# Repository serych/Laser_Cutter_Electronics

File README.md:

# Laser cutter electronics for Fluid NC

This is small laser cutter electronics board. The main goal of the development was to achieve a **board width of less than 4 cm** so that it could be easily mounted on standard 4020 profiles used in the construction of laser engravers. 
The board is designed for use with [Fluid NC software](http://wiki.fluidnc.com/en/home). 
## Electronics concept
The electronics are based on the **ESP32 WROOM** module, containing two **TMC2130 SPI** stepper motor drivers, a **PWM output for the laser**, and a **Micro SD card slot**. 
The initial programming of the ESP32 processor must be done via an **external USB-UART converter**; the board has a connector for this purpose. 
**!!!Make sure that the converter supplies the board with 3.3V (and not 5V)!!!** 
Further upgrades can be done using OTA. 

The board also includes an **Attiny 412 processor**, which controls a WS2812 **color status LED** (internal with the option of connecting one additional external LED). This processor can be programmed via the UPDI interface (there is a connector on the board for this purpose), which is again connected to the USB-UART converter. 
*The Attiny 412 processor with status LED is an **optional accessory**; the board works even without it.* 
## Files
The schematic and PCB layout were created in [KiCad](https://kicad.org) 9. The Gerber and drilling files for PCB production are stored in the "Gerber" directory.

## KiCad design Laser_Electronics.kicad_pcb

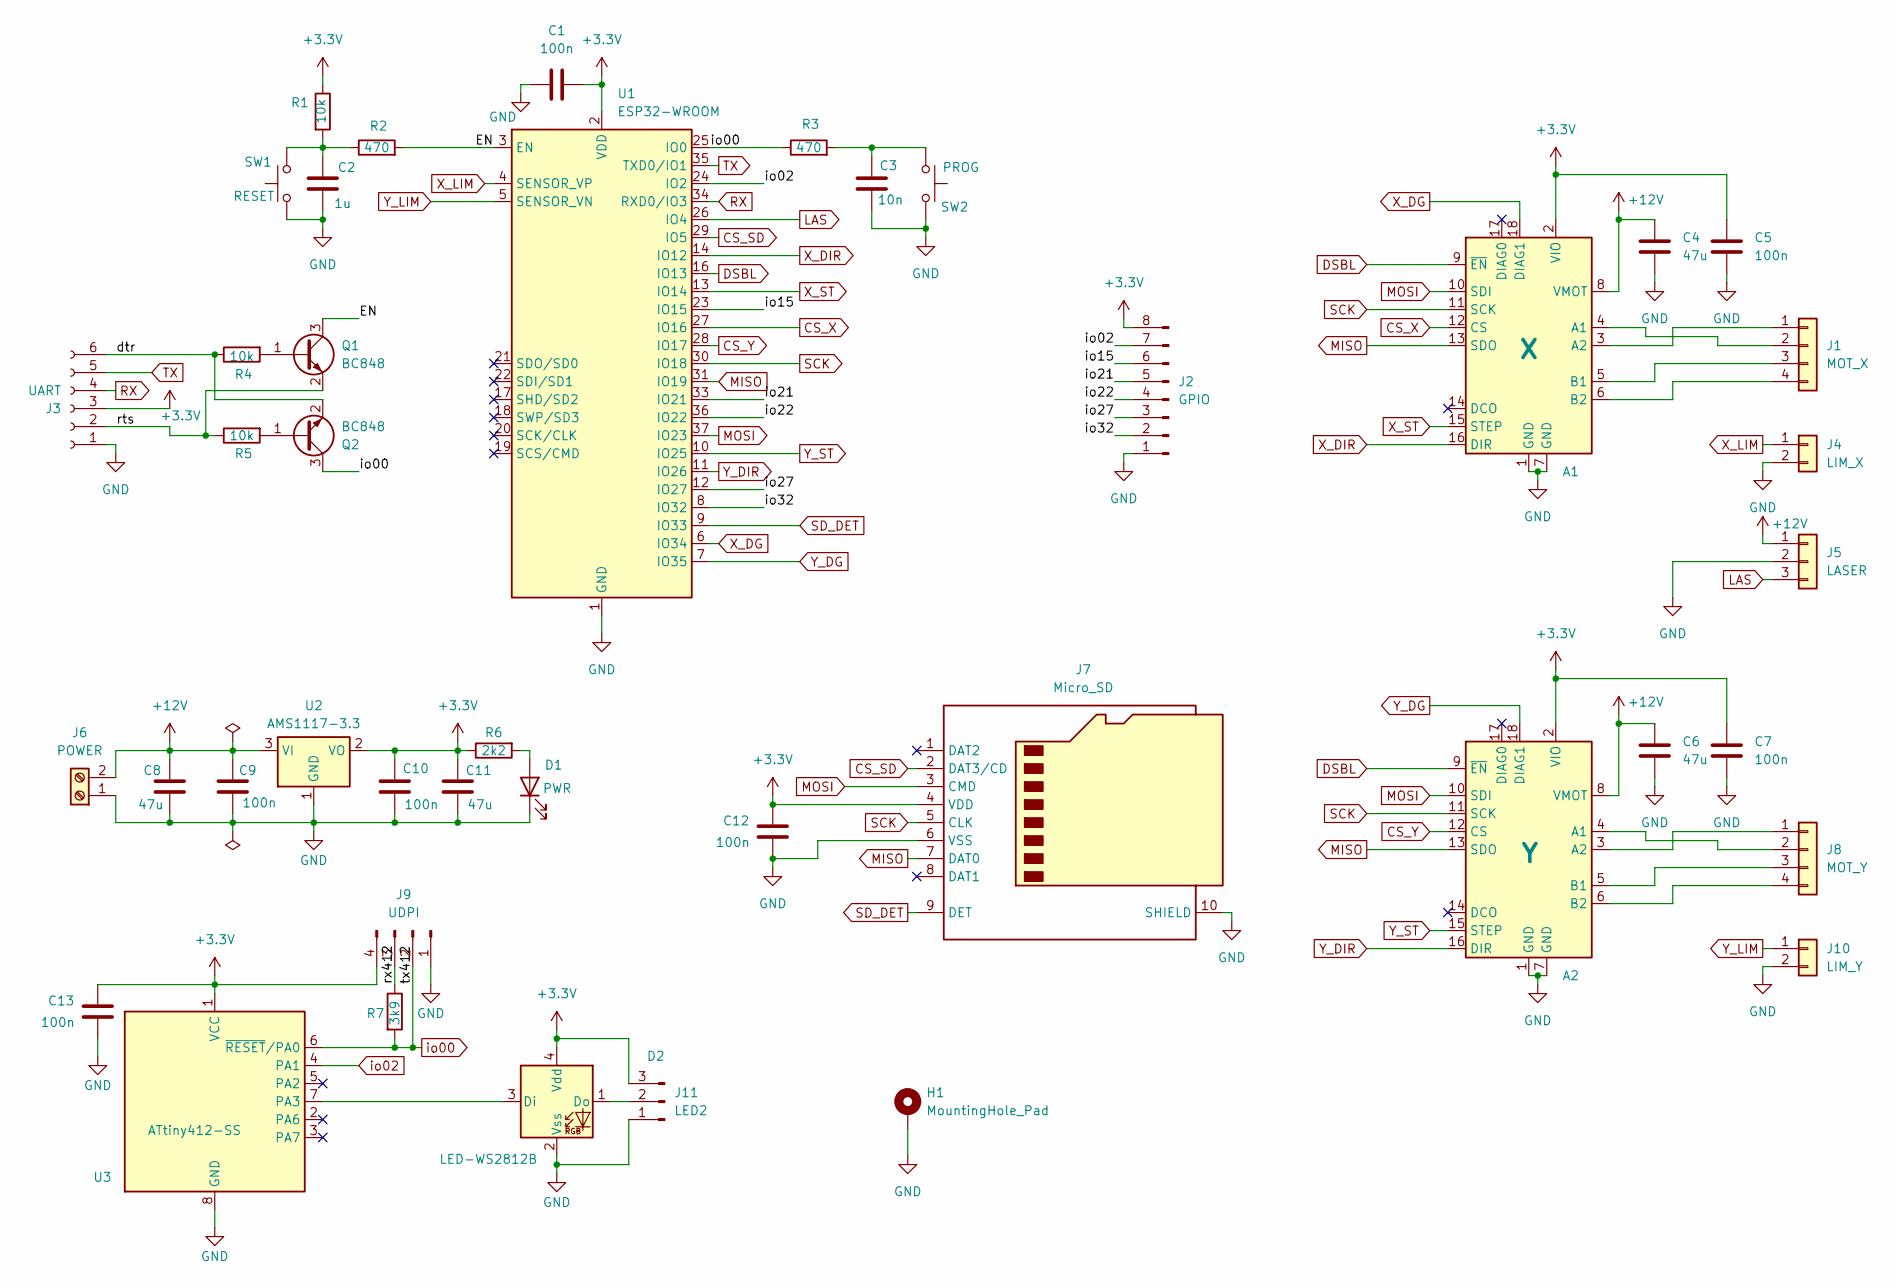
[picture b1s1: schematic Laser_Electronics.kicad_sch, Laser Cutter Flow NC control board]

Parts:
A1: X; Pololu_Breakout-18_15.2x20.3mm
A2: Y; Pololu_Breakout-18_15.2x20.3mm
C1, C5, C7, C9, C10, C12, C13: 100n; C_0603_1608Metric
C2: 1u; C_0603_1608Metric
C3: 10n; C_0603_1608Metric
C4, C6, C8, C11: 47u; CP_Elec_6.3x7.7
D1: PWR; LED_0603_1608Metric
D2: LED-WS2812B; LED_Cree-PLCC4_2x2mm_CW
H1: MountingHole_Pad; MountingHole_3.2mm_M3_DIN965_Pad
J1: MOT_X; JST_EH_B4B-EH-A_1x04_P2.50mm_Vertical
J2: GPIO; PinHeader_1x08_P2.54mm_Vertical
J3: UART; PinSocket_1x06_P2.54mm_Vertical
J4: LIM_X; JST_PH_B2B-PH-K_1x02_P2.00mm_Vertical
J5: LASER; JST_EH_B3B-EH-A_1x03_P2.50mm_Vertical
J6: POWER; TerminalBlock_RND_205-00045_1x02_P5.00mm_Horizontal
J7: Micro_SD; J_SD_Card-micro_socket_A
J8: MOT_Y; JST_EH_B4B-EH-A_1x04_P2.50mm_Vertical
J9: UDPI; PinHeader_1x04_P2.54mm_Vertical
J10: LIM_Y; JST_PH_B2B-PH-K_1x02_P2.00mm_Vertical
J11: LED2; PinHeader_1x03_P2.54mm_Vertical
Q1, Q2: BC848; SOT-23
R1, R4, R5: 10k; R_0603_1608Metric
R2, R3: 470; R_0603_1608Metric
R6: 2k2; R_0603_1608Metric
R7: 3k9; R_0603_1608Metric
SW1: RESET; SW_3x3mm
SW2: PROG; SW_3x3mm
U1: ESP32-WROOM; ESP32-WROOM-32
U2: AMS1117-3.3; SOT-223-3_TabPin2
U3: ATtiny412-SS; SOIC-8_3.9x4.9mm_P1.27mm

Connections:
+3.3V: A1.2 (VIO), A2.2 (VIO), C1.2, C5.2, C7.2, C10.1, C11.1, C12.2, C13.2, D2.4 (Vdd), J2.8, J3.3, J7.4 (VDD), J9.4, J11.3, R1.1, R6.1, U1.2 (VDD), U2.2 (VO), U3.1 (VCC)
+12V: A1.8 (VMOT), A2.8 (VMOT), C4.1, C6.1, C8.1, C9.1, J5.1, J6.2, U2.3 (VI)
/EN: Q1.3 (C), R2.2, U1.3 (EN)
/dtr: J3.6, Q2.2 (E), R4.1
/io15: J2.6, U1.23 (IO15)
/io21: J2.5, U1.33 (IO21)
/io22: J2.4, U1.36 (IO22)
/io27: J2.3, U1.12 (IO27)
/io32: J2.2, U1.8 (IO32)
/rts: J3.2, Q1.2 (E), R5.1
/rx412: J9.3, R7.1
CS_SD: J7.2 (DAT3/CD), U1.29 (IO5)
CS_X: A1.12 (CS), U1.27 (IO16)
CS_Y: A2.12 (CS), U1.28 (IO17)
DSBL: A1.9 (~EN), A2.9 (~EN), U1.16 (IO13)
GND: A1.1 (GND), A1.7 (GND), A2.1 (GND), A2.7 (GND), C1.1, C2.2, C3.2, C4.2, C5.1, C6.2, C7.1, C8.2, C9.2, C10.2, C11.2, C12.1, C13.1, D1.1 (K), D2.2 (Vss), H1.1, J2.1, J3.1, J4.2, J5.2, J6.1, J7.6 (VSS), J7.10 (SHIELD), J9.1, J10.2, J11.1, SW1.1, SW2.2, U1.1 (GND), U1.15 (GND), U1.38 (GND), U1.39 (GND), U2.1 (GND), U3.8 (GND)
LAS: J5.3, U1.26 (IO4)
MISO: A1.13 (SDO), A2.13 (SDO), J7.7 (DAT0), U1.31 (IO19)
MOSI: A1.10 (SDI), A2.10 (SDI), J7.3 (CMD), U1.37 (IO23)
unnamed: A1.4 (A1), J1.2
unnamed: A1.3 (A2), J1.1
unnamed: A1.5 (B1), J1.3
unnamed: A1.6 (B2), J1.4
unnamed: A2.4 (A1), J8.2
unnamed: A2.3 (A2), J8.1
unnamed: A2.5 (B1), J8.3
unnamed: A2.6 (B2), J8.4
unnamed: C2.1, R1.2, R2.1, SW1.2
unnamed: C3.1, R3.2, SW2.1
unnamed: D1.2 (A), R6.2
unnamed: D2.3 (Di), U3.7 (PA3)
unnamed: D2.1 (Do), J11.2
unnamed: Q1.1 (B), R4.2
unnamed: Q2.1 (B), R5.2
RX: J3.4, U1.34 (RXD0/IO3)
SCK: A1.11 (SCK), A2.11 (SCK), J7.5 (CLK), U1.30 (IO18)
SD_DET: J7.9 (DET), U1.9 (IO33)
TX: J3.5, U1.35 (TXD0/IO1)
X_DG: A1.18 (DIAG1), U1.6 (IO34)
X_DIR: A1.16 (DIR), U1.14 (IO12)
X_LIM: J4.1, U1.4 (SENSOR_VP)
X_ST: A1.15 (STEP), U1.13 (IO14)
Y_DG: A2.18 (DIAG1), U1.7 (IO35)
Y_DIR: A2.16 (DIR), U1.11 (IO26)
Y_LIM: J10.1, U1.5 (SENSOR_VN)
Y_ST: A2.15 (STEP), U1.10 (IO25)
io00: J9.2, Q2.3 (C), R3.1, R7.2, U1.25 (IO0), U3.6 (~RESET/PA0)
io02: J2.7, U1.24 (IO2), U3.4 (PA1)

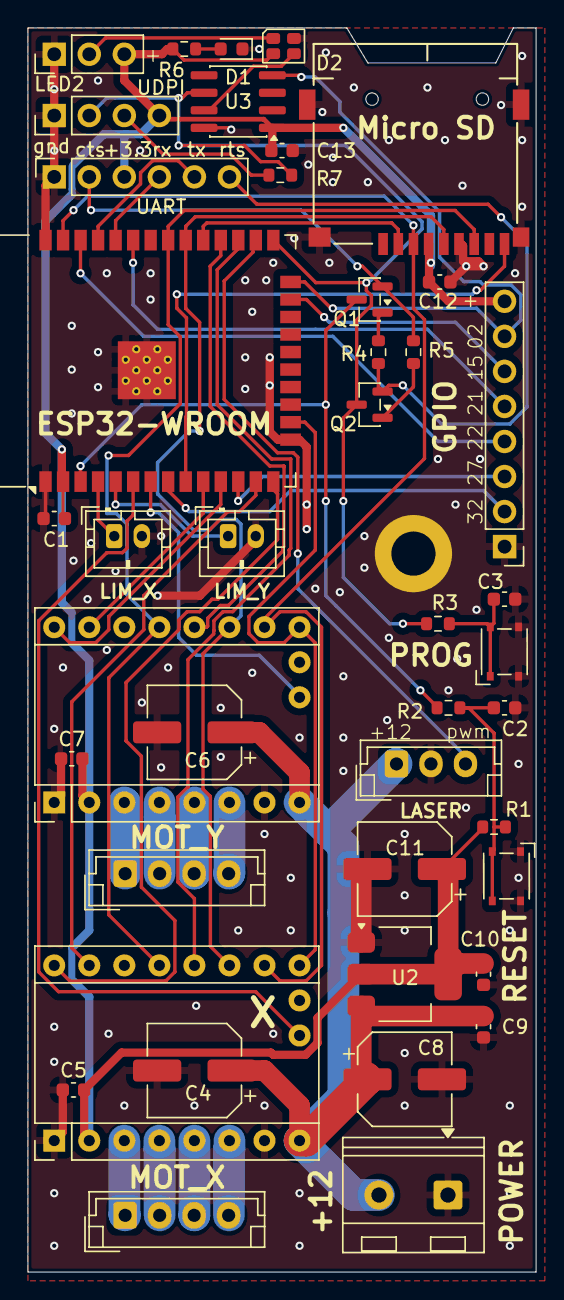
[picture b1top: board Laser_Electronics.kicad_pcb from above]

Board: 2 copper layers, 36.8 x 90.2 mm, 43 parts (0 on the bottom side), 48 nets.

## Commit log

2025-10-14 Založení projektu
2025-10-14 Hotové schéma
2025-10-27 ver 1 layout
2025-10-27 Version 1 - fabrication files
2025-10-27 README.md
2025-10-27 Add GNU General Public License v3
2025-10-27 UART reset circuit error repaired
2025-10-28 rev2 silkscreen + MiniLaser.yaml

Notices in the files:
Laser_Electronics.kicad_pcb:
© JaSoSe 2025
